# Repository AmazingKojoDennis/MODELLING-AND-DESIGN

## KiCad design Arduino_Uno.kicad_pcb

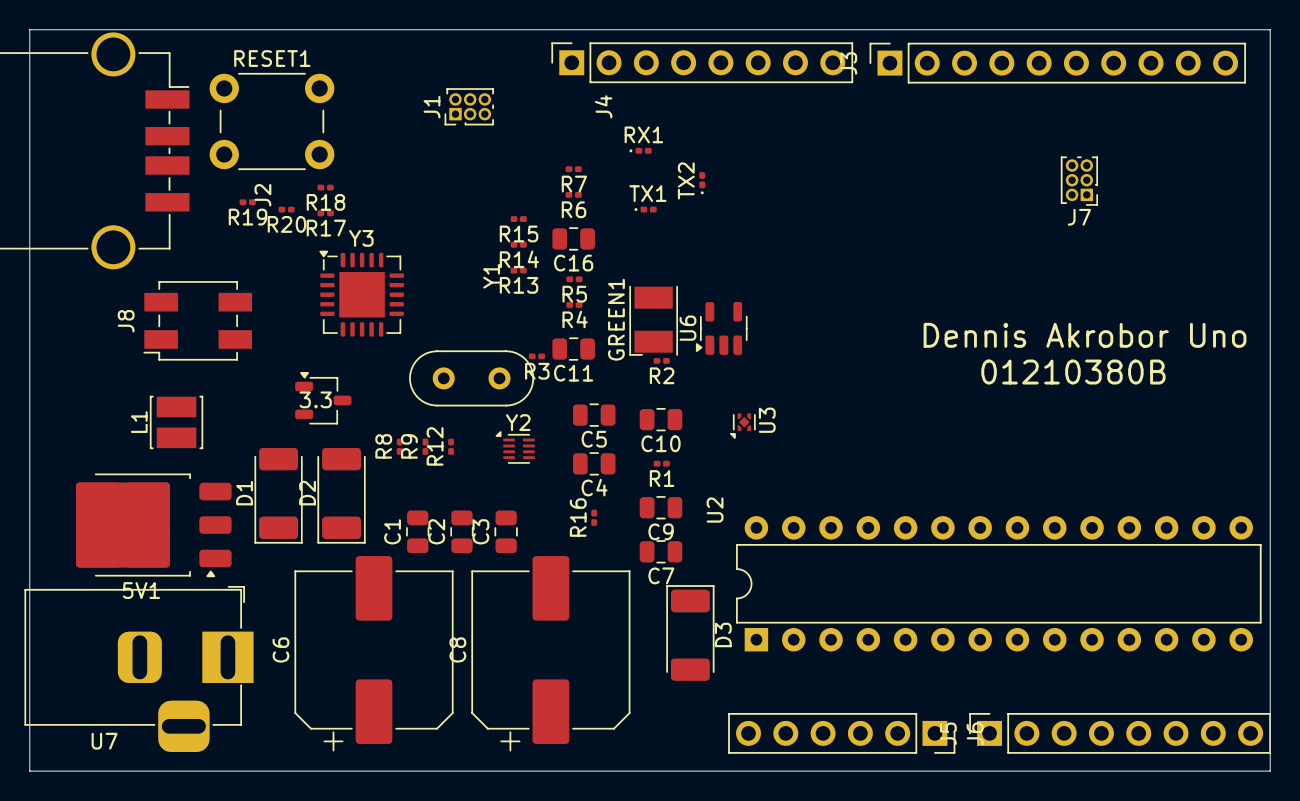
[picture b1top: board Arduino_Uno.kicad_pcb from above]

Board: 2 copper layers, 84.5 x 50.5 mm, 56 parts (0 on the bottom side), 42 nets, no tracks yet.

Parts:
3.3: LMV358; TSOT-23
5V1: LMV358; TO-252-3_TabPin2
C1, C2, C3, C4, C5, C7, C9, C16: C; C_0805_2012Metric
C6, C8: C_Polarized; CP_Elec_10x10.5
C10: 22p; C_0805_2012Metric
C11: 22P; C_0805_2012Metric
D1, D2, D3: D; D_2010_5025Metric_Pad1.52x2.65mm_HandSolder
GREEN1: ON; LED_PLCC-2_3.4x3.0mm_AK
J1, J7: Conn_02x03_Odd_Even; PinHeader_2x03_P1.00mm_Vertical
J2: USB_B; USB_A_TE_292303-7_Horizontal
J3: Conn_01x10_Socket; PinSocket_1x10_P2.54mm_Vertical
J4, J5: Conn_01x08_Socket; PinSocket_1x08_P2.54mm_Vertical
J6: Conn_01x06_Socket; PinSocket_1x06_P2.54mm_Vertical
J8: Conn_02x02_Odd_Even; Samtec_HLE-102-02-xxx-DV_2x02_P2.54mm_Horizontal
L1: BLM21; L_Cenker_CKCS3012
R1, R2, R3, R4, R5, R6, R7, R8, R9, R12, R13, R14, R15, R16, R17, R18, R19, R20: R; R_0201_0603Metric
RESET1: SolderJumper_2_Open; SW_PUSH_6mm
RX1: YELLOW; LED_0201_0603Metric
TX1, TX2: YELLOW; LED_0201_0603Metric
U2: ATmega328P-P; DIP-28_W7.62mm
U3: NCP115AMX250TCG; OnSemi_XDFN4-1EP_1.0x1.0mm_EP0.52x0.52mm
U6: LP2985-1.8; SOT-23-5
U7: LM7805_TO220; BarrelJack_Horizontal
Y1: Crystal; Crystal_HC52-6mm_Vertical
Y2: Crystal; TDFN-8_1.4x1.6mm_P0.4mm
Y3: Crystal_GND3_Small; TQFN-20-1EP_5x5mm_P0.65mm_EP3.1x3.1mm

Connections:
5+: C2.1, C3.1, C5.1, C5.2, C6.1, C7.1, C7.2, C8.2, C9.1, C9.2, C10.1, C11.1, C16.2, D1.1 (K), D2.1 (K), GREEN1.1 (K), J1.1, J1.2, J1.6, J3.7, J4.2, J4.5, J7.2, J7.6, R2.1, R4.2, R6.2, R7.2, R15.1, R16.1, R17.2, R18.1, TX1.1 (K), U2.7 (VCC), U2.8 (GND), U2.20 (AVCC), U2.28 (UGND), U3.1 (OUT), U3.2 (GND), U3.3 (EN), U3.5 (GND), U6.1 (VIN), U6.2 (GND), U6.3 (ON/~OFF), U7.1 (VI), U7.2 (GND), Y3.3
unnamed: 5V1.3 (+), R18.2, R19.1
unnamed: D1.2 (A), J1.5, R4.1
unnamed: D2.2 (A), R17.1, U2.1 (~RESET/PC6)
unnamed: D3.2 (A), U7.3 (VO)
unnamed: C8.1, D3.1 (K), U3.4 (IN)
unnamed: GREEN1.2 (A), R15.2, R16.2
unnamed: C4.2, J2.4 (GND), L1.2
unnamed: J2.3 (D+), R1.1
unnamed: J2.2 (D-), R3.1
unnamed: J2.5 (Shield), L1.1
unnamed: J3.1, U2.14 (PB0)
unnamed: J3.2, U2.15 (PB1)
unnamed: J3.3, U2.16 (PB2)
unnamed: J3.4, J7.4, U2.17 (PB3)
unnamed: J3.5, J7.1, U2.18 (PB4)
unnamed: J3.6, J7.3, U2.19 (PB5)
unnamed: C2.2, J3.8
unnamed: J4.3, J7.5, R9.1, U2.9 (XTAL1/PB6), Y3.2
unnamed: J5.1, U2.2 (PD0)
unnamed: J5.2, U2.3 (PD1)
unnamed: J5.3, U2.4 (PD2)
unnamed: J5.4, U2.5 (PD3)
unnamed: J5.5, U2.6 (PD4)
unnamed: J5.6, U2.11 (PD5)
unnamed: J5.7, R12.2, U2.12 (PD6)
unnamed: J5.8, R8.2, U2.13 (PD7)
unnamed: J6.1, U2.23 (PC0)
unnamed: J6.2, U2.24 (PC1)
unnamed: J6.3, U2.25 (PC2)
unnamed: J6.4, U2.26 (PC3)
unnamed: J6.5, U2.27 (PC4)
unnamed: C1.1, RESET1.1 (A), RESET1.2 (B)
unnamed: R7.1, RX1.2 (A)
unnamed: R20.1, TX1.2 (A)
unnamed: R6.1, TX2.2 (A)
unnamed: C11.2, R5.2, Y1.2, Y2.2
unnamed: C10.2, R5.1, Y1.1, Y2.1
unnamed: C1.2, R2.2
unnamed: R9.2, U2.10 (XTAL2/PB7), Y3.1
unnamed: C16.1, U6.4 (BP)
USBVCC: J2.1 (VBUS), U2.21 (AREF)

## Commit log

2024-04-29 Add files via upload
    This is an LM555 timer connection
